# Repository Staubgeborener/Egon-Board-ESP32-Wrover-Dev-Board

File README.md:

These are parts (created with eagle) for a ESP32 Dev Board. You also find the bom file inside.
The board has support for a sd card adapter and also for LiPo. Keep in mind, that this pcb is for the ESP32 **Wrover** NOT for the wroom (different pinout)!

All necessary parts are in this repo. So you can just download this and create the pcb at your manufactory of trust.

But just take a closer look:

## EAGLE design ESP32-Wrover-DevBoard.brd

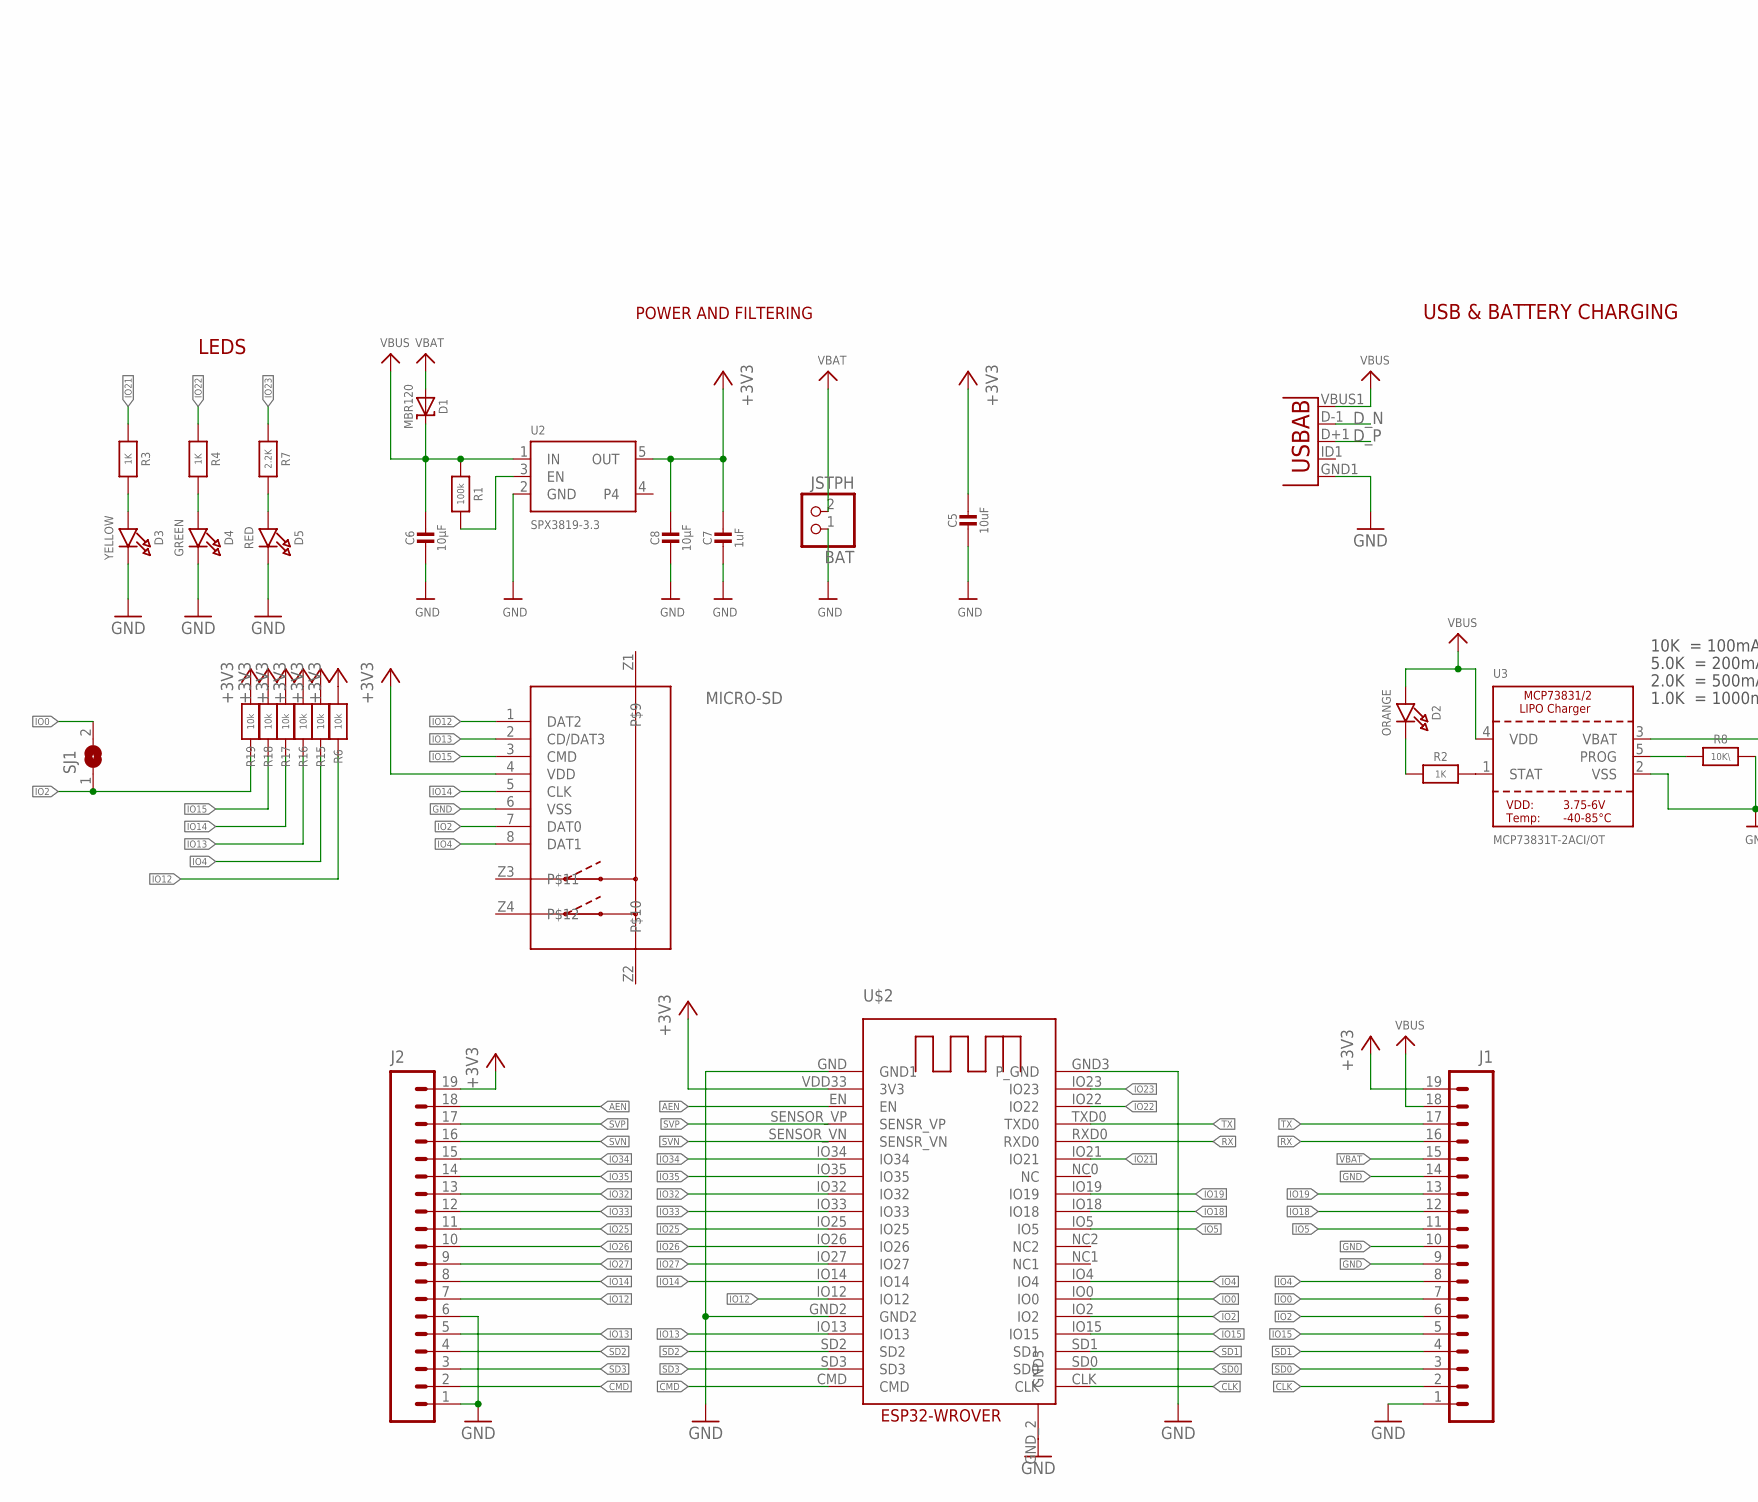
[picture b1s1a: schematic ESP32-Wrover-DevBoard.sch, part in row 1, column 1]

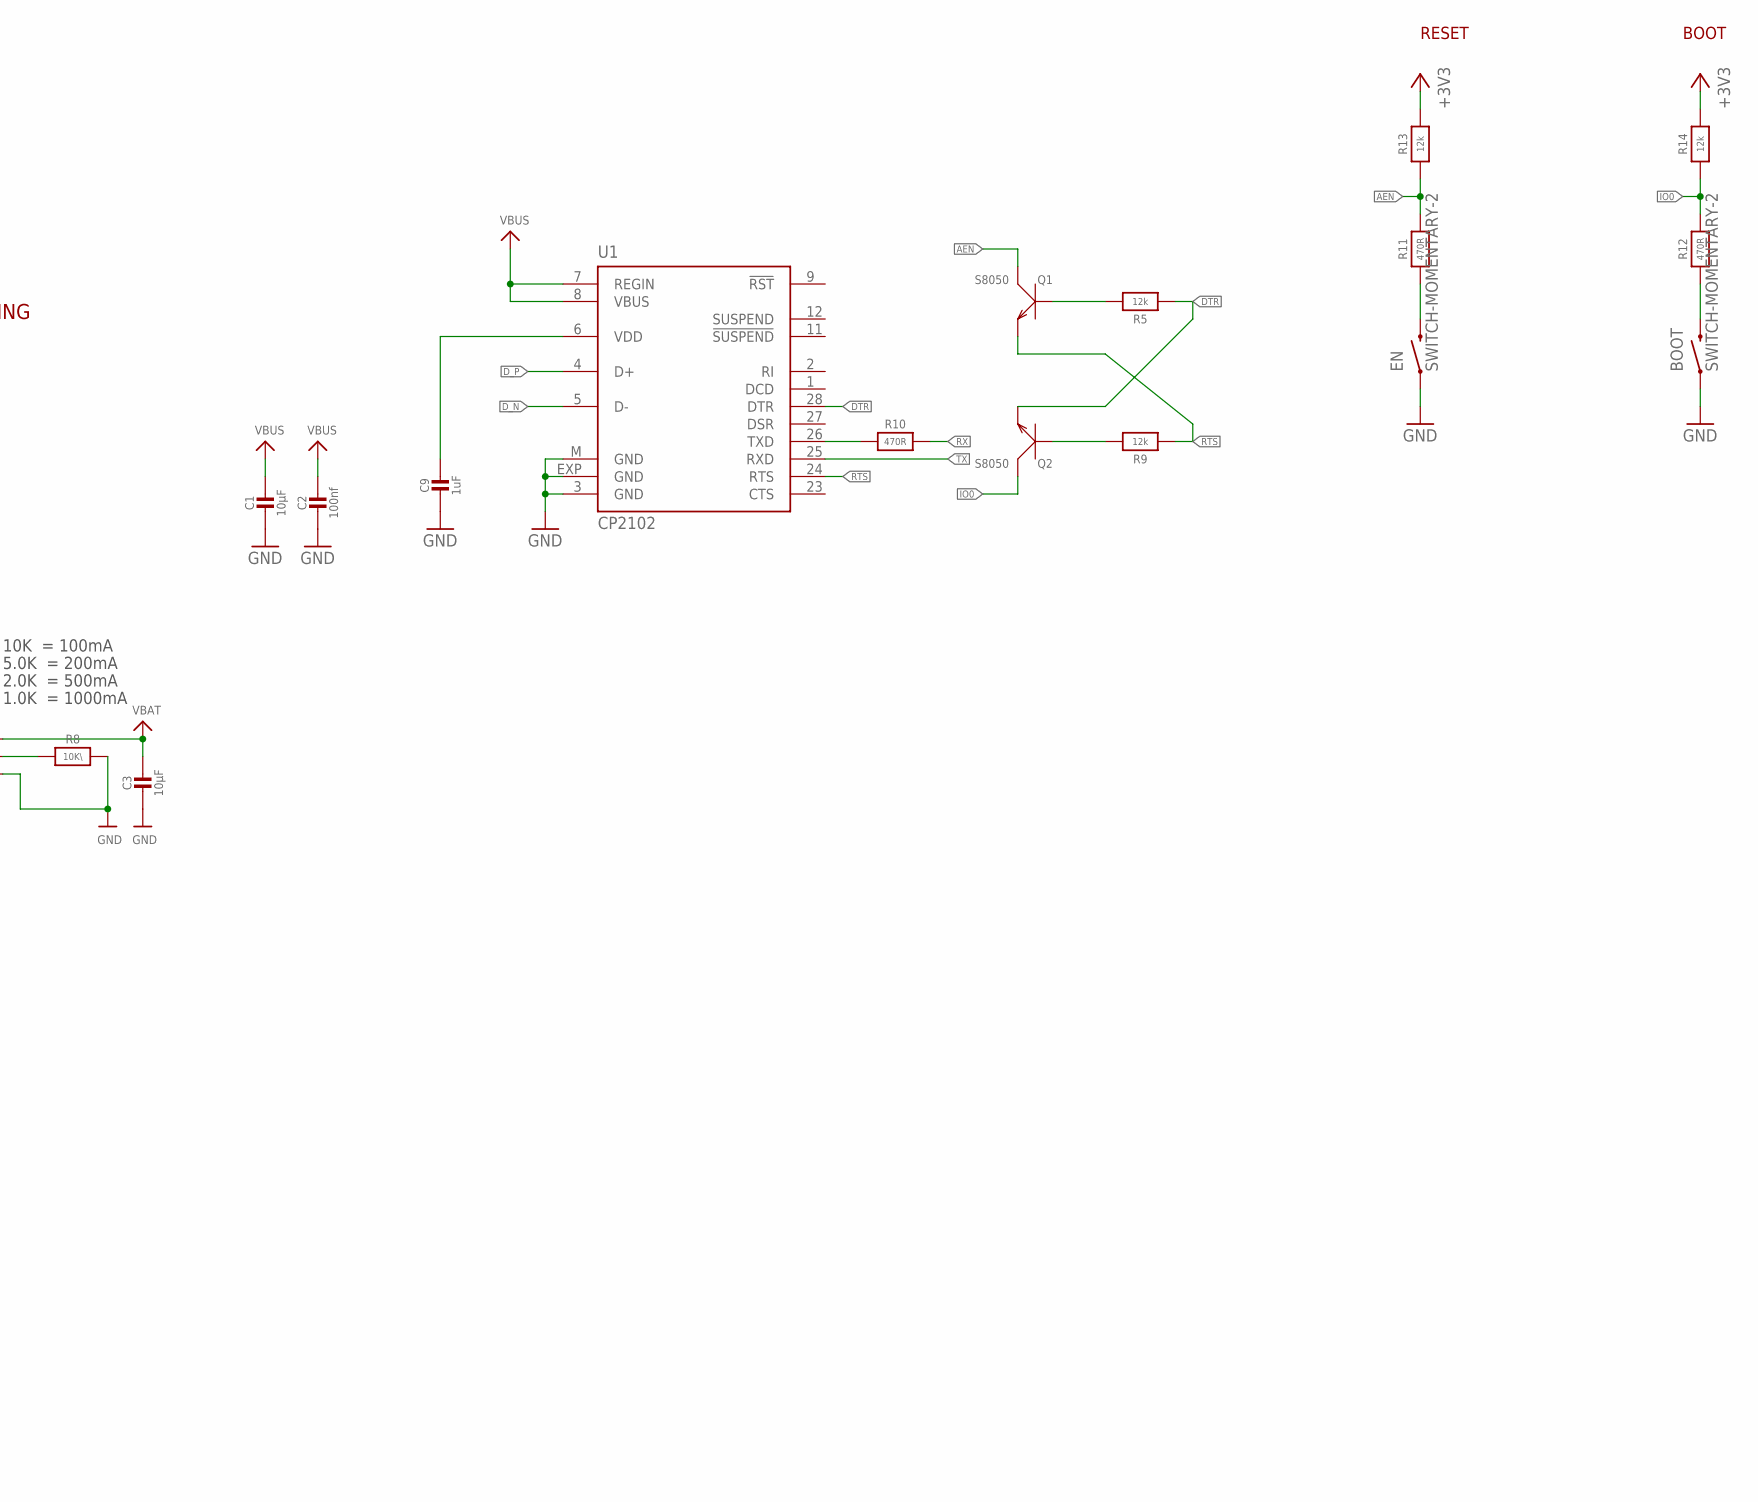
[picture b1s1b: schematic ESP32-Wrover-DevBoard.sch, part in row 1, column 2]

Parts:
BAT: JSTPH; JSTPH2
BOOT: SWITCH-MOMENTARY-2; WS-TRS-6.0X3.5MM-TACT-SWITCH_SMD
C1, C3, C6, C8: 10µF; 0805-NO
C2: 100nf; 0603-NO
C5: 10uF; 0805-NO
C7, C9: 1uF; 0603-NO
D1: MBR120; SOD-123
D2: ORANGE; CHIPLED_0805_NOOUTLINE
D3: YELLOW; CHIPLED_0805_NOOUTLINE
D4: GREEN; CHIPLED_0805_NOOUTLINE
D5: RED; CHIPLED_0805_NOOUTLINE
EN: SWITCH-MOMENTARY-2; WS-TRS-6.0X3.5MM-TACT-SWITCH_SMD
J1, J2: M191X19_NO_SILK; 1X19_NO_SILK
M-USB: USB""; USB-MICRO-SMD
MICRO-SD: 693072010801
Q1, Q2: S8050; SOT-23
R1: 100k; 0603-NO
R2, R3, R4: 1K; 0603-NO
R5, R9, R13, R14: 12k; 0603-NO
R6, R15, R16, R17, R18, R19: 10k; 0603-NO
R7: 2.2K; 0603-NO
R8: 10K\; 0603-NO
R10, R11, R12: 470R; 0603-NO
SJ1: SJ
U1: CP2102; MLP28
U2: SPX3819-3.3; SOT23-5
U3: MCP73831T-2ACI/OT; SOT23-5
U$2: ESP32-WROVER

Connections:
+3V3: C5.1, C7.1, C8.1, J1.19, J2.19, MICRO-SD.4 (VDD), R6.1, R13.2, R14.2, R15.1, R16.1, R17.1, R18.1, R19.1, U2.5 (OUT), U$2.VDD33 (3V3)
AEN: J2.18, Q1.3 (C), R11.2, R13.1, U$2.EN
CLK: J1.2, U$2.CLK
CMD: J2.2, U$2.CMD
DTR: Q2.2 (E), R5.1, U1.28 (DTR)
D_N: M-USB.D-1 (D-), U1.5 (D-)
D_P: M-USB.D+1 (D+), U1.4 (D+)
GND: BAT.1, BOOT.1, C1.2, C2.2, C3.2, C5.2, C6.2, C7.2, C8.2, C9.2, D3.C, D4.C, D5.C, EN.1, J1.1, J1.9, J1.10, J1.14, J2.1, J2.6, M-USB.GND1 (GND), MICRO-SD.6 (VSS), R8.2, U1.3 (GND), U1.EXP (GND), U1.M (GND), U2.2 (GND), U3.2 (VSS), U$2.GND (GND1), U$2.GND2, U$2.GND3 (P_GND), U$2.GND_2 (GND3)
IO0: J1.7, Q2.3 (C), R12.2, R14.1, SJ1.2, U$2.IO0
IO2: J1.6, MICRO-SD.7 (DAT0), R19.2, SJ1.1, U$2.IO2
IO4: J1.8, MICRO-SD.8 (DAT1), R15.2, U$2.IO4
IO5: J1.11, U$2.IO5
IO12: J2.7, MICRO-SD.1 (DAT2), R6.2, U$2.IO12
IO13: J2.5, MICRO-SD.2 (CD/DAT3), R16.2, U$2.IO13
IO14: J2.8, MICRO-SD.5 (CLK), R17.2, U$2.IO14
IO15: J1.5, MICRO-SD.3 (CMD), R18.2, U$2.IO15
IO18: J1.12, U$2.IO18
IO19: J1.13, U$2.IO19
IO21: R3.1, U$2.IO21
IO22: R4.1, U$2.IO22
IO23: R7.1, U$2.IO23
IO25: J2.11, U$2.IO25
IO26: J2.10, U$2.IO26
IO27: J2.9, U$2.IO27
IO32: J2.13, U$2.IO32
IO33: J2.12, U$2.IO33
IO34: J2.15, U$2.IO34
IO35: J2.14, U$2.IO35
unnamed: D2.C, R2.1
unnamed: D5.A, R7.2
unnamed: R2.2, U3.1 (STAT)
unnamed: R8.1, U3.5 (PROG)
unnamed: R10.1, U1.26 (TXD)
unnamed: D4.A, R4.2
unnamed: Q1.1 (B), R5.2
unnamed: Q2.1 (B), R9.2
unnamed: C9.1, U1.6 (VDD)
unnamed: EN.2, R11.1
unnamed: BOOT.2, R12.1
unnamed: D3.A, R3.2
NX1: R1.2, U2.3 (EN)
RTS: Q1.2 (E), R9.1, U1.24 (RTS)
RX: J1.16, R10.2, U$2.RXD0
SD0: J1.3, U$2.SD0
SD1: J1.4, U$2.SD1
SD2: J2.4, U$2.SD2
SD3: J2.3, U$2.SD3
SVN: J2.16, U$2.SENSOR_VN (SENSR_VN)
SVP: J2.17, U$2.SENSOR_VP (SENSR_VP)
TX: J1.17, U1.25 (RXD), U$2.TXD0
VBAT: BAT.2, C3.1, D1.A, J1.15, U3.3 (VBAT)
VBUS: C1.1, C2.1, C6.1, D1.C, D2.A, J1.18, M-USB.VBUS1 (VBUS), R1.1, U1.7 (REGIN), U1.8 (VBUS), U2.1 (IN), U3.4 (VDD)

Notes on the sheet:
POWER AND FILTERING
BOOT
10K = 100mA
5.0K = 200mA
2.0K = 500mA
1.0K = 1000mA
USB & BATTERY CHARGING
LEDS
RESET

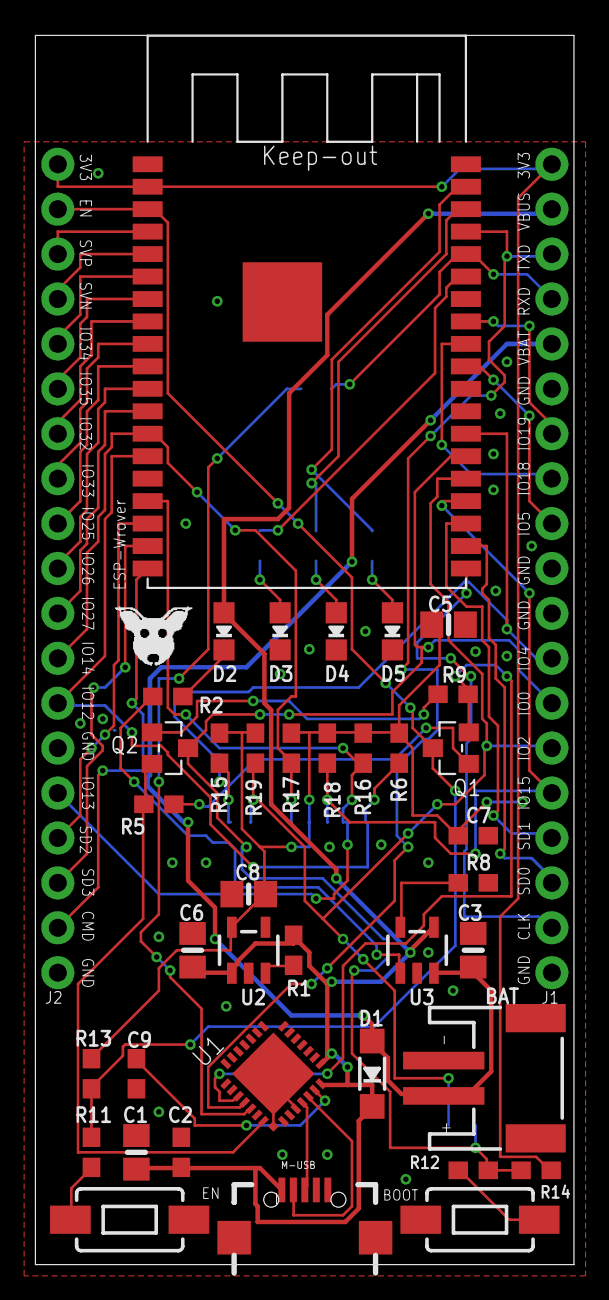
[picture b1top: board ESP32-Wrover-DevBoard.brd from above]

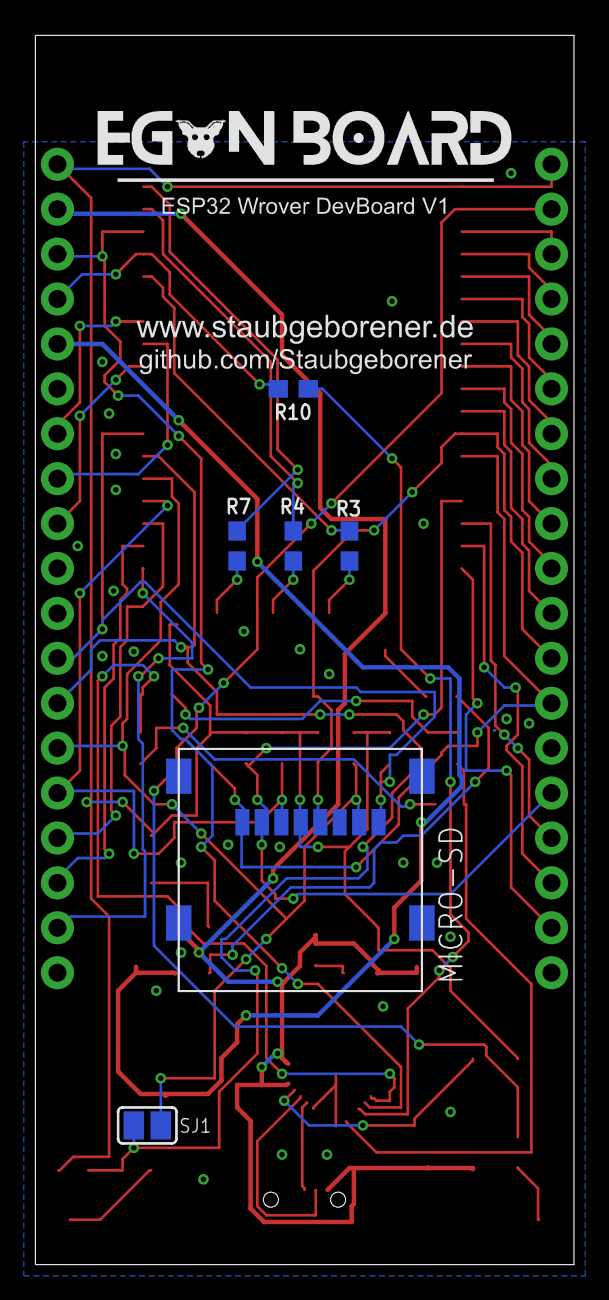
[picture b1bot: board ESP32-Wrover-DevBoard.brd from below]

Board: 2 copper layers, 30.5 x 69.5 mm, 48 parts (7 on the bottom side), 52 nets.

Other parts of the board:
U$8: EGON-HEAD
U$9: EGON-LOGO-SCALE-0.5

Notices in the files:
parts and their libraries:
microbuilder: This work is placed in the public domain, and may be freely used for commercial and non-commercial work with the following conditions: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
SparkFun-Connectors: Licensing: Creative Commons ShareAlike 4.0 International - https://creativecommons.org/licenses/by-sa/4.0
